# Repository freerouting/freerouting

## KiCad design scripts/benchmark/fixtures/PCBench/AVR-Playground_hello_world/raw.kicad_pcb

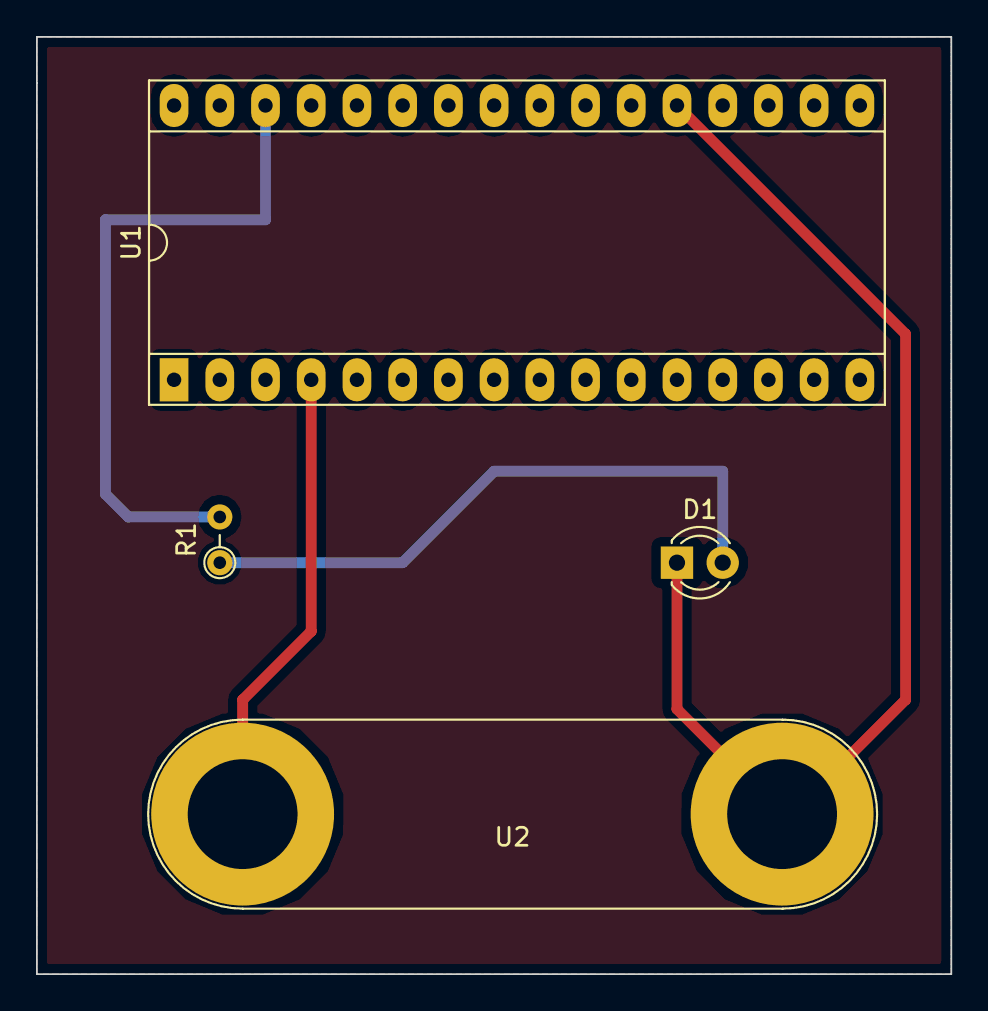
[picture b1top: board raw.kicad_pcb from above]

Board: 2 copper layers, 50.8 x 52.1 mm, 4 parts (0 on the bottom side), 4 nets.

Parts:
D1: LED; LED_D3.0mm
R1: 1k; R_Axial_DIN0204_L3.6mm_D1.6mm_P2.54mm_Vertical
U1: ATMEGA328P-AU; DIP-32_W15.24mm_Socket_LongPads
U2: myConn2; Banana_Jack_2Pin

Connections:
+5V: U1.4, U2.1
GND: D1.1, U1.21, U2.2
unnamed: D1.2, R1.1
unnamed: R1.2, U1.30

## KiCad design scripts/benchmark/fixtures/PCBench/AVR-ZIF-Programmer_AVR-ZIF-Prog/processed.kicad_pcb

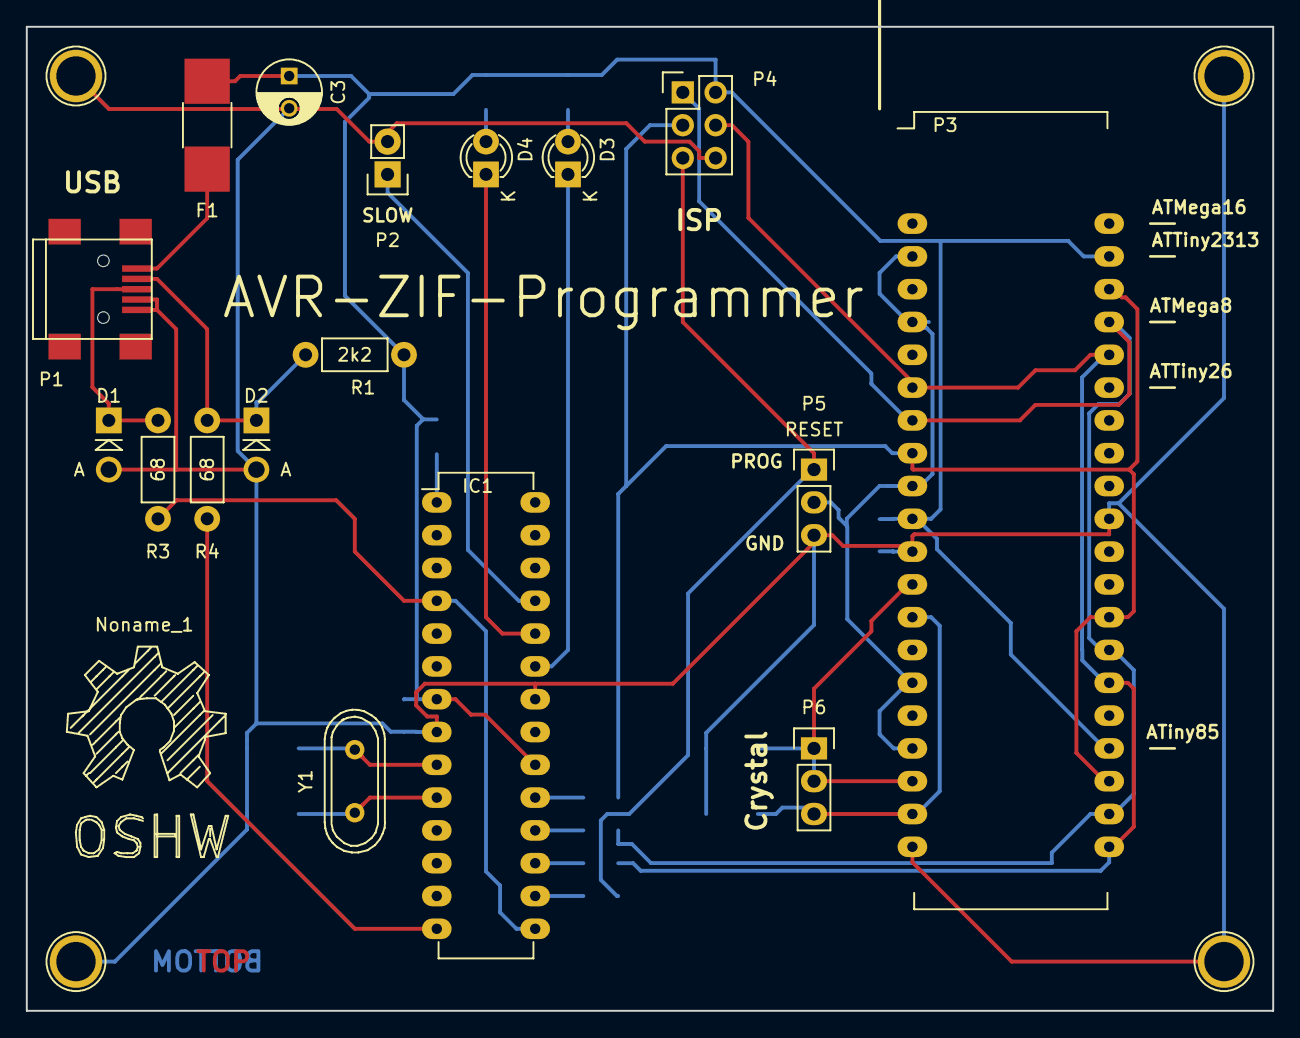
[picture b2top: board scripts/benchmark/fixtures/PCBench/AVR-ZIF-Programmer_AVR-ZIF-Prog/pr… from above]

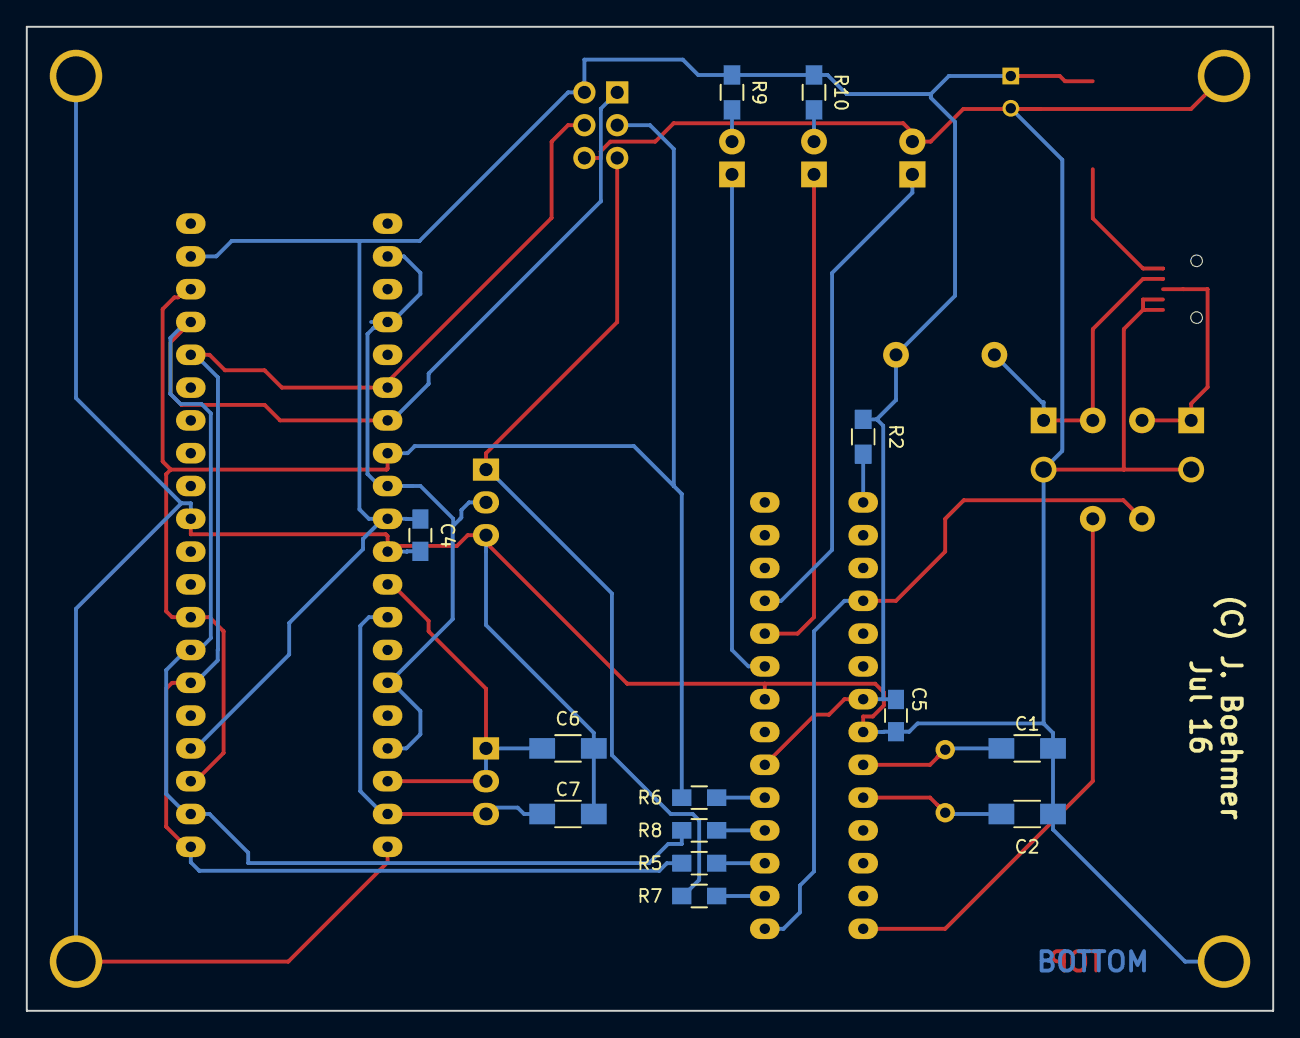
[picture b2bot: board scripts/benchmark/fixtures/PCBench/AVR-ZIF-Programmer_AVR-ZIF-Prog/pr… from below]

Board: 2 copper layers, 96.5 x 76.2 mm, 35 parts (13 on the bottom side), 26 nets.

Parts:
C1, C2, C6, C7: 15p; C_1206_HandSoldering
C3: 10u; C_Radial_D5_L6_P2.5
C4, C5: 100n; C_0805_HandSoldering
D1, D2: 3V6; Diode_DO-41_SOD81_Vertical_AnodeUp
D3: green; LED-3MM
D4: red; LED-3MM
F1: Poly 500mA; R_1812_HandSoldering
IC1: ATMEGA8-P; DIP-28_W7.62mm_LongPads
Noname_1: Symbol_OSHW-Logo_SilkScreen_BIG
P1: USB_B; USB_Mini-B
P2: SLOW_SCK; Pin_Header_Straight_1x02
P3: ZIF40; ZIF-40_W15.24mm_LongPads
P4: AVR-ISP; Pin_Header_Straight_2x03
P5: RESET; Pin_Header_Straight_1x03
P6: XTAL; Socket_Strip_Straight_1x03
P7, P8, P9, P10: MOUNT; 1pin
R1: 2k2; Resistor_Horizontal_RM7mm
R2: 10k; R_0805_HandSoldering
R3, R4: 68; Resistor_Horizontal_RM7mm
R5, R6, R7, R8: 220; R_0805_HandSoldering
R9, R10: 1k; R_0805_HandSoldering
Y1: 12MHz; Crystal_HC49-U_Vertical

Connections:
/D+: IC1.4, IC1.15, R3.1
/D-: IC1.14, R4.1
/LED1: D3.1, IC1.23
/LED2: D4.1, IC1.24
/MISO: P3.7, P3.22, P3.27, P3.37, P4.1, R8.2
/MOSI: P3.6, P3.21, P3.26, P3.36, P4.4, R5.2
/RST: P3.2, P3.4, P3.9, P3.15, P3.17, P5.2
/RST1: P4.5, P5.1, R7.2
/SCK: P3.8, P3.23, P3.28, P3.38, P4.3, R6.2
/SLOW: IC1.25, P2.1
/XTAL1: C6.1, P3.12, P3.18, P6.1, P6.2
/XTAL2: C7.1, P3.13, P3.19, P6.3
GND: C1.2, C2.1, C3.2, C4.2, C5.2, C6.2, C7.2, D1.2, D2.2, IC1.8, IC1.22, P1.4, P1.5, P2.2, P3.11, P3.20, P3.31, P4.6, P5.3, P7.1, P8.1, P9.1, P10.1
unnamed: C1.1, IC1.9, Y1.2
unnamed: C2.2, IC1.10, Y1.1
unnamed: D1.1, P1.3, R3.2
unnamed: D2.1, P1.2, R1.2, R4.2
unnamed: D3.2, R9.2
unnamed: D4.2, R10.2
unnamed: F1.2, P1.1
unnamed: IC1.1, R2.2
unnamed: IC1.16, R7.1
unnamed: IC1.17, R5.1
unnamed: IC1.18, R8.1
unnamed: IC1.19, R6.1
VCC: C3.1, C4.1, C5.1, F1.1, IC1.7, IC1.20, P3.10, P3.24, P3.39, P4.2, R1.1, R2.1, R9.1, R10.1

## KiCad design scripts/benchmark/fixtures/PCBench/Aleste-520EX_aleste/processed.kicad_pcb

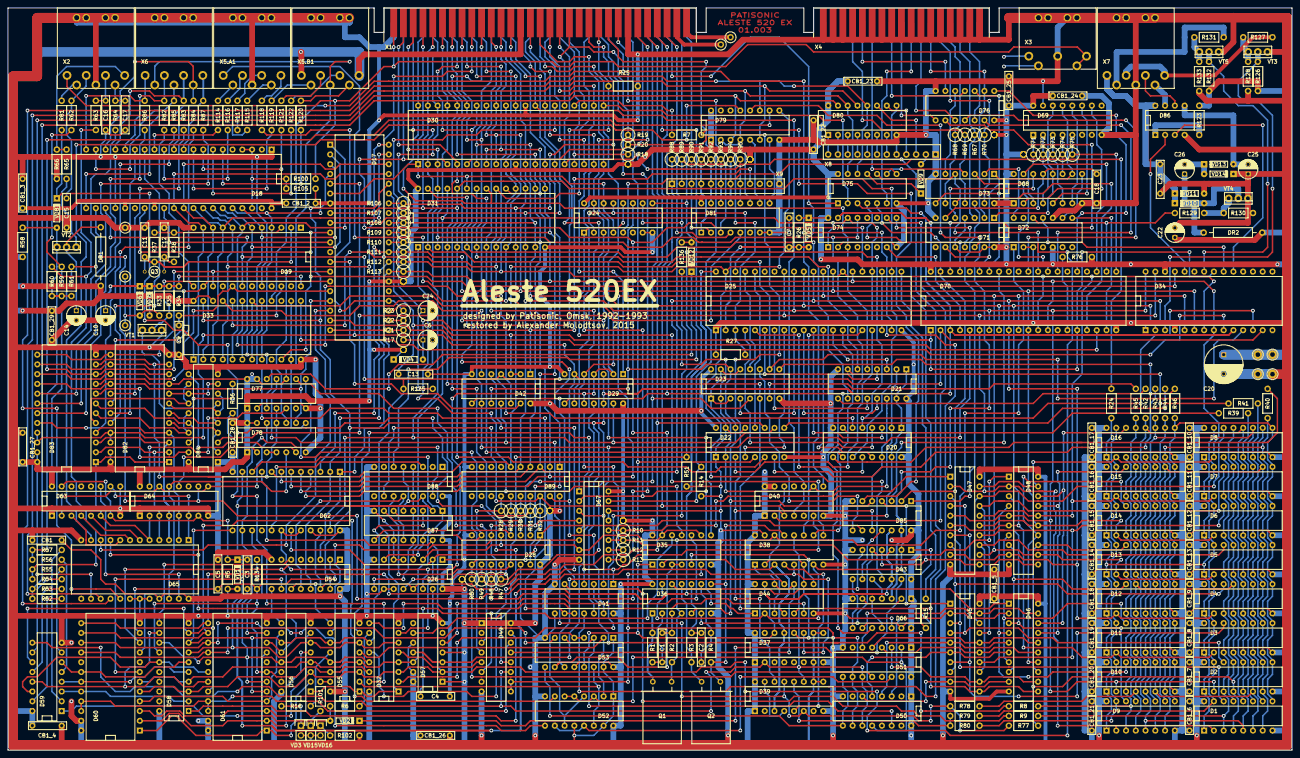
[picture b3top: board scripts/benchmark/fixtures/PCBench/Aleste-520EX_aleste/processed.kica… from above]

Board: 2 copper layers, 334.0 x 193.0 mm, 313 parts (0 on the bottom side), 451 nets.

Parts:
C1, C2, C3, C4, C5, C7, C9, C11, C12, C13, C15, C16, C17, C18, C23: CAP; C_Disc_D7.5_P2.5
C6, C10, C14, C22, C24, C25, C26: CAPP; C_Radial_D5_L6_P2.5
C20: CAPP; C_Radial_D10_L16_P5
CB1, CB1_2, CB1_3, CB1_4, CB1_5, CB1_6, CB1_7, CB1_8, CB1_9, CB1_10, CB1_11, CB1_12, CB1_13, CB1_14, CB1_15, CB1_16, CB1_17, CB1_18, CB1_19, CB1_20, CB1_21, CB1_22, CB1_23, CB1_24, CB1_25, CB1_26, CB1_27, CB1_28, CB1_29: CAP; C_Disc_D7.5_P2.5
D1, D2, D3, D4, D5, D6, D7, D8, D9, D10, D11, D12, D13, D14, D15, D16: 565РУ7; DIP-16
D17: 580ВВ55; DIP-40
D18: AY-3-8910; DIP-40
D19: 512ВИ1; DIP-24
D20, D21, D22, D23, D52, D53: 555КП2; DIP-16
D24, D81: 555КП7; DIP-16
D25: 1809ВГ6; DIP-40
D26: 555КП12; DIP-16
D28, D67: 556РТ4; DIP-16
D29, D44: 555ЛЛ1; DIP-14
D30: Z80; DIP-40
D31: 27512; DIP-28
D32, D55, D56, D59, D68, D79: 555ТМ9; DIP-16
D33: 580ВИ53; DIP-24
D34: 580ВВ51; DIP-28
D35, D85: 555ЛИ1; DIP-14
D36, D42, D73: 555ЛН1; DIP-14
D37: 555ИЕ10; DIP-16
D38: 555КП11; DIP-16
D39, D49, D50, D51: 555ИР11; DIP-16
D40, D57, D66, D71, D77: 555ТМ2; DIP-14
D41, D75, D78: 555ЛА3; DIP-14
D43: 555ЛЕ1; DIP-14
D45, D46, D47, D48: 555ИР22; DIP-20
D54, D74: 555ИД4; DIP-16
D58, D84: 555ИР23; DIP-20
D60, D61, D82, D83: 1802ИР1; DIP-24
D62, D65: 573РФ2; DIP-24
D63, D64: 561ИЕ10; DIP-16
D69: 155РЕ3; DIP-16
D70: 1810ВГ72; DIP-40
D72: 555ИЕ5; DIP-14
D76: 555ЛН2; DIP-14
D80: 555ИД10; DIP-16
D86: 170АП2; DIP-8
D87, D88: 555ИР32; DIP-16
D89: 555АП6; DIP-20
DR1, DR2: INDUCTOR; Choke_Horizontal_RM15mm
P1, P2, P3, P4, P5, P6, P7, P7_2, P8: PIN
Q1: 16 MHz; Crystal_HC49-U_Horizontal_Typ1
Q2: 13.333 MHz; Crystal_HC49-U_Horizontal_Typ1
Q3: QUARTZ; Crystal_Round_Vertical_5mm
R1, R2, R3, R4, R5, R6, R7, R8, R9, R14, R15, R16, R24, R25, R26, R27, R33, R34, R35, R36, R37, R38, R39, R40, R41, R42, R43, R44, R45, R46, R51, R52, R53, R54, R55, R56, R57, R58, R59, R60, R61, R62, R63, R64, R65, R66, R76, R77, R78, R79, R80, R81, R82, R83, R84, R85, R86, R87, R100, R101, R102, R105, R114, R115, R116, R117, R118, R119, R120, R121, R122, R123, R126, R127, R128, R129, R130, R131, R132, R133, R134, R135, R136: RES; Resistor_Horizontal_RM7.5mm
R10, R11, R12, R13, R17, R18, R19, R20, R21, R22, R23, R28, R29, R30, R31, R32, R47, R48, R49, R50, R67, R68, R69, R70, R71, R72, R73, R74, R75, R88, R89, R90, R91, R92, R93, R94, R95, R106, R107, R108, R109, R110, R111, R112, R113: RES; Resistor_Vertical_RM2.5mm
VD1, VD2, VD4, VD5, VD6, VD7, VD8, VD9, VD10, VD12, VD13, VD14: DIODE_MY; Diode_DO-35_SOD27_Horizontal_RM7.5
VD3, VD15, VD16: LED_MY; Pin_Header_Straight_1x02
VD11: ZDIODE_MY; Diode_DO-35_SOD27_Horizontal_RM7.5
VT1, VT2, VT3, VT4, VT5: NPN; KT315_KT361
X1: SLOT-62; SLOT_62
X2, X5.A1, X5.B1, X6, X7: CONN-7S; DNR-8F1R
X3: CONN-5S; DNR-5F1R
X4: SLOT-34
X8, X9: CONN-12; FB-12

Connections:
/AGND: P4.1, X1.A30
/AVCC: P3.1, X1.A31
/CPU/A0: D30.30, D31.10, D33.19, D41.2, D42.9, D67.3, D70.5, X1.B9
/CPU/A1: D20.6, D30.31, D31.9, D33.20, X1.A9
/CPU/A2: D20.10, D30.32, D31.8, X1.B8
/CPU/A3: D21.6, D30.33, D31.7, X1.A8
/CPU/A4: D21.10, D30.34, D31.6, X1.B7
/CPU/A5: D22.6, D30.35, D31.5, X1.A7
/CPU/A6: D23.6, D30.36, D31.4, D44.4, X1.B6
/CPU/A7: D21.11, D30.37, D31.3, D74.13, X1.A6
/CPU/A8: D17.9, D20.5, D25.24, D26.4, D30.38, D31.25, D34.12, D74.1, D74.14, X1.B5
/CPU/A9: D17.8, D20.11, D25.22, D26.12, D30.39, D31.24, X1.A5
/CPU/A10: D21.5, D30.40, D31.21, D74.3, X1.B4
/CPU/A11: D17.6, D24.4, D24.14, D30.1, D31.23, X1.A4
/CPU/A12: D23.10, D30.2, D31.2, D34.11, X1.B3
/CPU/A13: D22.10, D29.13, D30.3, D31.26, D62.23, X1.A3
/CPU/A14: D25.25, D26.3, D28.5, D30.4, D35.9, D35.13, D67.7, X1.B2
/CPU/A15: D26.13, D28.6, D30.5, D54.14, D62.22, D67.4, D89.1, X1.A2
/CPU/BUFFER0: D47.1, D67.12, R10.1
/CPU/BUFFER1: D48.1, D67.11, R11.1
/CPU/CLK: D30.6, D39.14, D40.3, R20.1, X1.B25
/CPU/D0: D1.2, D9.2, D17.34, D25.33, D30.14, D31.11, D34.27, D47.2, D48.2, D62.8, D70.6, D89.6, R106.1, X1.B13
/CPU/D1: D2.2, D10.2, D17.33, D25.32, D30.15, D31.12, D34.28, D47.5, D48.5, D62.7, D70.7, D89.5, R107.1, X1.A13
/CPU/D2: D3.2, D11.2, D17.32, D25.31, D30.12, D31.13, D34.1, D47.6, D48.6, D62.6, D70.8, D89.4, R108.1, X1.B12
/CPU/D3: D4.2, D12.2, D17.31, D25.30, D30.8, D31.15, D34.2, D47.9, D48.9, D62.5, D70.9, D89.3, R109.1, X1.A12
/CPU/D4: D5.2, D13.2, D17.30, D25.29, D30.7, D31.16, D34.5, D47.12, D48.12, D62.4, D70.10, D89.2, R110.1, X1.B11
/CPU/D5: D6.2, D14.2, D17.29, D25.28, D30.9, D31.17, D34.6, D47.15, D48.15, D62.3, D70.11, R111.1, X1.A11
/CPU/D6: D7.2, D15.2, D17.28, D25.27, D30.10, D31.18, D34.7, D47.16, D48.16, D54.13, D62.2, D70.12, R112.1, X1.B10
/CPU/D7: D8.2, D16.2, D17.27, D25.26, D30.13, D31.19, D34.8, D47.19, D48.19, D54.3, D62.1, D70.13, R113.1, X1.A10
/CPU/HY: C3.1, D25.40, D43.12, D85.12
/CPU/LOP: D43.10, D66.4
/CPU/PROM0: D55.7, D67.5
/CPU/PROM1: D55.10, D67.6
/CPU/RAMDIS: D67.15, R14.2, X1.A23
/CPU/ROM0: D35.10, D57.5
/CPU/ROM1: D35.12, D57.9
/CPU/ROMDIS: D31.22, R25.1, X1.A22
/CPU/SINT: D66.3, D79.12, D85.13
/CPU/~BUSAK: D30.23, X1.B19
/CPU/~BUSRQ: D30.25, R19.1, X1.A19
/CPU/~HALT: D30.18, X1.B17
/CPU/~INT: D30.16, R15.2, X1.A18
/CPU/~INTA: D29.8, D66.10, X1.A29
/CPU/~IORD: D17.5, D29.6, D34.13, D41.13, D70.2, D82.21, D82.22, D83.21, D83.22, D89.19
/CPU/~IORQ: D26.14, D29.2, D29.4, D29.10, D30.20, D62.18, D62.20, X1.A16
/CPU/~IOWR: D17.36, D29.3, D29.12, D33.23, D34.10, D41.12, D54.15, D70.3, D74.15
/CPU/~M1: D29.9, D30.27, X1.A15
/CPU/~MREQ: D30.19, D44.1, D67.2, X1.B14
/CPU/~NMI: D30.17, R18.1, X1.B18
/CPU/~RAMEN: D67.9, R13.1, X1.B22
/CPU/~RD: D29.5, D30.21, D67.1, D75.2, X1.B16
/CPU/~RESET: D18.23, D19.18, D32.1, D42.4, D55.1, D56.1, R135.1, X1.A21
/CPU/~RESET*: C24.1, D30.26, R135.2
/CPU/~RFSH: D30.28, D40.4, D40.10, X1.B15
/CPU/~ROMEN: D31.20, D67.10, R12.1, X1.B21
/CPU/~WAIT: D30.24, R7.2
/CPU/~WR: D29.1, D30.22, X1.A17
/Clocks & CRTC/1CY: D64.12, D78.2
/Clocks & CRTC/1M: D18.22, D37.11, D38.5, D64.10
/Clocks & CRTC/2CY: D64.13, D65.22, D78.5
/Clocks & CRTC/2M: D37.12, D38.2, D38.6, D44.9
/Clocks & CRTC/3CY: D63.2, D64.9, D64.14, D78.12
/Clocks & CRTC/4M: D35.2, D37.13, D38.3, D39.3
/Clocks & CRTC/8M: D35.1, D37.14, D44.13, D53.13
/Clocks & CRTC/13MHZ: D36.8, D38.13, Q2.1, R4.2
/Clocks & CRTC/16MHZ: D36.4, D38.14, D72.1, Q1.1, R2.2
/Clocks & CRTC/CAS: D39.12, R79.1, R80.1
/Clocks & CRTC/CBUF: D25.21, D43.4, D47.11, D48.11
/Clocks & CRTC/CURSOR: D25.19, D33.16, X1.B23
/Clocks & CRTC/DEN: D25.18, D77.12
/Clocks & CRTC/HIGHT: D38.1, D44.10, D44.12, D49.13
/Clocks & CRTC/HX: D25.39, D33.18, D43.11, D77.3, D79.9
/Clocks & CRTC/HY*: D17.18, D65.10
/Clocks & CRTC/KK0: D65.14, D79.3, D80.15
/Clocks & CRTC/KK1: D65.15, D75.13, D79.4, D80.14
/Clocks & CRTC/KK2: D65.16, D79.6, D80.13
/Clocks & CRTC/KK3: D65.17, D75.12, D79.11, D80.12
/Clocks & CRTC/L0: D24.2, D24.13, D25.38
/Clocks & CRTC/L1: D23.12, D25.37
/Clocks & CRTC/L2: D22.12, D25.36
/Clocks & CRTC/L.PEN: D25.3, R27.2, X1.A24
/Clocks & CRTC/MK0: D63.6, D64.2, D65.5, D82.1, D83.1
/Clocks & CRTC/MK1: D64.3, D65.4, D82.2, D83.2
/Clocks & CRTC/MK2: D64.4, D65.3, D82.3, D83.3
/Clocks & CRTC/MK3: D64.5, D65.2, D82.4, D83.4
/Clocks & CRTC/RAS: D39.6, D39.13, D42.11, D77.11, R77.1, R78.1
/Clocks & CRTC/SINT*: D65.11, D79.13
/Clocks & CRTC/SYNC*: C4.2, D49.6, D65.9
/Clocks & CRTC/V1: D20.4, D25.4
/Clocks & CRTC/V2: D20.12, D25.5
/Clocks & CRTC/V3: D21.4, D25.6
/Clocks & CRTC/V4: D21.12, D25.7
/Clocks & CRTC/V5: D22.4, D25.8
/Clocks & CRTC/V6: D23.4, D25.9
/Clocks & CRTC/V7: D21.13, D25.10
/Clocks & CRTC/V8: D20.3, D25.11
/Clocks & CRTC/V9: D20.13, D25.12
/Clocks & CRTC/V10: D21.3, D25.13
/Clocks & CRTC/V11: D25.14, D38.10
/Clocks & CRTC/V13: D25.16, D38.11
/Clocks & CRTC/V14: D22.3, D25.17
/Clocks & CRTC/V1113: D24.1, D24.12, D38.9
/Clocks & CRTC/VCLK: D36.13, D38.7, D43.2, D44.2, D45.1, D85.4
/Clocks & CRTC/XTAL: D37.2, D38.12, D39.11, D49.11, D50.11, D51.11, D59.9
/Clocks & CRTC/~3CY: D77.4, D78.11, D82.11, D83.11
/Clocks & CRTC/~RESET2: C7.2, D25.2, R26.1, VD5.2
/FDC/DISCINT: D17.19, D70.18
/FDC/DSKRDY: D70.35, D71.9, D76.3
/FDC/DW: D70.22, D72.12, R129.1
/FDC/EXRG: D44.5, D74.10
/FDC/FP0: D68.3, D69.1, R71.1
/FDC/FP1: D68.4, D69.2, R72.1
/FDC/FP2: D68.6, D69.3, R73.1
/FDC/FP3: D68.11, D69.4, R74.1
/FDC/RDD: D68.15, D70.23
/FDC/RESET: C13.2, D17.35, D34.21, D42.2, D42.3, D70.1, D70.16
/FDC/RSCLK: D34.20, D72.11
/FDC/RW/S: D70.39, D75.5, D85.2
/FDC/WGPTCLK: D70.19, D72.8
/FDC/WRC: D69.5, D70.21, R75.1
/FDC/XD0: D32.3, D55.3, D56.3, D57.2, D58.3, D60.5, D62.9, D71.12, D87.15
/FDC/~DIR: D76.8, X4.A9
/FDC/~DRIVE0: D76.6, X4.A5
/FDC/~DRIVE1: D75.8, X4.A6
/FDC/~GATE: D71.2, D76.2, X4.A12
/FDC/~INDEX: D73.11, R69.1, X4.A4
/FDC/~MOTOR: D76.4, X4.A8
/FDC/~RDATA: D71.3, R67.1, X4.A15
/FDC/~SIDE: D76.12, X4.A16
/FDC/~STEP: D75.6, X4.A10
/FDC/~TRAC0: D73.13, R70.1, X4.A13
/FDC/~WRDAT: D76.10, X4.A11
/FDC/~WRTPRT: D73.9, R68.1, X4.A14
/Gate Array/4ST: D35.3, D35.4, D53.10
/Gate Array/8ST: D44.11, D53.11
/Gate Array/"A": D26.7, D87.5, D87.14, D88.5, D88.14
/Gate Array/"B": D26.9, D87.4, D87.13, D88.4, D88.13
/Gate Array/B: C15.1, R62.1, X2.4
/Gate Array/BLAKS: D32.10, R6.2
/Gate Array/BLANK: D59.1, R6.1, VD2.2
/Gate Array/C0: D58.2, D59.3, D60.20
/Gate Array/C1: D58.5, D59.4, D60.19
/Gate Array/C2: D58.6, D59.6, D60.18
/Gate Array/C3: D58.9, D59.11, D61.20
/Gate Array/C4: D58.12, D59.13, D61.19
/Gate Array/C5: D58.15, D59.14, D61.18
/Gate Array/CBORDER: D54.6, D58.11
/Gate Array/COLOR: C5.2, D54.2, D60.11, D61.11, R134.1
/Gate Array/CS53: D32.12, D42.5
/Gate Array/G: C16.1, R63.1, X2.5
/Gate Array/HIGHTX: D32.5, D49.5
/Gate Array/HIGHTY: D32.2, R136.2
/Gate Array/HIGHTZ: D24.9, R136.1, VD12.2, X1.B31
/Gate Array/LED0: D55.12, R16.1
/Gate Array/LED1: D55.15, R101.1
/Gate Array/LUM: R65.2, R66.2, X2.7
/Gate Array/M0: D28.7, D87.10, D89.14, R28.1
/Gate Array/M1: D28.4, D87.9, D89.15, R29.1
/Gate Array/M2: D28.3, D87.7, D89.16, R30.1
/Gate Array/M3: D28.2, D87.6, D89.17, R31.1
/Gate Array/M4: D28.15, D85.10, D88.10, D89.18, R32.1, X1.A28
/Gate Array/MAP14: D24.3, D24.15, D28.12, R47.1, X1.A26
/Gate Array/MAP15: D22.5, D28.11, R48.1, X1.B26
/Gate Array/MAP16: D22.11, D28.10, R49.1, X1.A27
/Gate Array/MAP17: D23.5, D28.9, R50.1, X1.B27
/Gate Array/MAP18: D23.11, D85.8
/Gate Array/MAPBLK: D28.13, D88.11, R51.2, X1.B28
/Gate Array/MAPER: D54.12, D87.12, D88.12
/Gate Array/MAPMOD: D26.2, D28.1, D32.7, D62.19, D85.9
/Gate Array/MODE: D54.11, D55.9
/Gate Array/MODE0: D52.14, D53.14, D55.2
/Gate Array/MODE1: D52.2, D53.2, D55.5
/Gate Array/MVI: D35.6, D49.9, D49.10, D50.10, D51.10
/Gate Array/NCOLOR: D54.9, D56.9
/Gate Array/NCOLOR0: D56.2, D60.1, D61.1
/Gate Array/NCOLOR1: D56.5, D60.2, D61.2
/Gate Array/NCOLOR2: D56.7, D60.3, D61.3
/Gate Array/NCOLOR3: D56.10, D60.4, D61.4
/Gate Array/NCOLOR4: D54.1, D56.12, D60.10, D61.10
/Gate Array/PAGE: D49.15, D58.1
/Gate Array/PX0: D51.12, D60.13, D61.13
/Gate Array/PX1: D52.7, D60.14, D61.14
/Gate Array/PX2: D52.9, D60.15, D61.15
/Gate Array/PX3: D53.7, D60.16, D61.16
/Gate Array/R: C17.1, R64.1, X2.3
/Gate Array/RRC: D50.9, D51.9, D53.9
/Gate Array/SOUND: R100.2, X1.A1, X2.6, X3.3, X3.5
/Gate Array/SYNC: D49.12, R81.1, VD8.1
/Gate Array/VD0: D45.2, D46.2, D50.3
/Gate Array/VD1: D45.5, D46.5, D50.4
/Gate Array/VD2: D45.6, D46.6, D50.5
/Gate Array/VD3: D45.9, D46.9, D50.6
/Gate Array/VD4: D45.12, D46.12, D51.3
/Gate Array/VD5: D45.15, D46.15, D51.4
/Gate Array/VD6: D45.16, D46.16, D51.5
/Gate Array/VD7: D45.19, D46.19, D51.6
/Gate Array/VRAMACC: D62.17, D88.3
/Gate Array/XD1: D32.4, D55.4, D56.4, D57.12, D58.4, D60.6, D62.10, D87.1
/Gate Array/XD2: D32.6, D55.6, D56.6, D58.7, D60.7, D62.11, D87.2
/Gate Array/XD3: D32.11, D55.11, D56.11, D58.8, D61.5, D62.13, D87.3
/Gate Array/XD4: D32.13, D55.13, D56.13, D58.13, D61.6, D62.14, D88.15
/Gate Array/XD5: D32.14, D55.14, D58.14, D61.7, D62.15
/Gate Array/~CSAY: D32.15, R36.1
/Gate Array/~FUTURE: D41.8, D52.4, D52.11
/Gate Array/~PAGE: D49.14, D60.21, D60.22, D61.21, D61.22
/Periphery/50/60: D17.22, R22.1
/Periphery/+12V: C23.2, D86.8, VD10.1, VD11.1, X7.6
/Periphery/-12V: C25.2, D86.5, VD13.2
/Periphery/AY0: D17.4, D18.37, D19.4, D33.8
/Periphery/AY1: D17.3, D18.36, D19.5, D33.7
/Periphery/AY2: D17.2, D18.35, D19.6, D33.6
/Periphery/AY3: D17.1, D18.34, D19.7, D33.5
/Periphery/AY4: D17.40, D18.33, D19.8, D33.4
/Periphery/AY5: D17.39, D18.32, D19.9, D33.3
/Periphery/AY6: D17.38, D18.31, D19.10, D33.2
/Periphery/AY7: D17.37, D18.30, D19.11, D33.1
/Periphery/BC1: D17.11, D18.29
/Periphery/BDIR: D17.10, D18.27
/Periphery/BUSY: D17.24, R23.1, R118.1
/Periphery/COMMON: D78.8, X5.B1.2, X6.1
/Periphery/DSR: D34.22, R132.2, VT5.C
/Periphery/DSR*: R131.1, X7.1
/Periphery/DTR: D34.24, D86.2
/Periphery/DTR*: D86.7, X7.3
/Periphery/FUTURE: D33.17, D41.9, D41.10
/Periphery/KM0: D80.1, X8.12
/Periphery/KM1: D80.2, X8.11
/Periphery/KM2: D80.3, X8.10
/Periphery/KM3: D80.4, X8.9
/Periphery/KM4: D80.5, X8.8
/Periphery/KM5: D80.6, X8.7
/Periphery/KM6: D80.7, X8.6
/Periphery/KM7: D80.9, X8.5
/Periphery/KM8: D80.10, X8.4
/Periphery/KM9: D80.11, X8.3
/Periphery/KM10: VD9.2, X8.2
/Periphery/KM11: D81.4, R88.1, X9.1
/Periphery/KM12: D81.3, R89.1, X9.2
/Periphery/KM13: D81.2, R90.1, X9.3
/Periphery/KM14: D81.1, R91.1, X9.4
/Periphery/KM15: D81.15, R92.1, X9.5
/Periphery/KM16: D81.14, R93.1, X9.6
/Periphery/KM17: D81.13, R94.1, X9.7
/Periphery/KM18: D81.12, R95.1, X9.8
/Periphery/KRS: D81.5, D84.3
/Periphery/KW0: D79.2, D81.11
/Periphery/KW1: D79.5, D81.10
/Periphery/KW2: D79.7, D81.9
/Periphery/KW3: D79.10, D82.10, D83.10
/Periphery/PB2: D17.20, D17.21, R21.1
/Periphery/PD0: D18.13, R114.1
/Periphery/PD1: D18.12, R116.1
/Periphery/PD2: D18.11, R117.1
/Periphery/PD3: D18.10, R115.1
/Periphery/PD4: D18.9, R119.1
/Periphery/PD5: D18.8, R121.1
/Periphery/PD6: D18.7, R122.1
/Periphery/PD7: D18.6, R120.1
/Periphery/RXC: D33.10, D34.25
/Periphery/RXD: D34.3, R126.1, VT3.C
/Periphery/SABC: D18.3, D18.4, D18.38, R100.1, R105.2
/Periphery/SBRES: C6.1, D42.1, R17.1, VD4.2, X9.9
/Periphery/STROBE: D17.13, D42.13
/Periphery/TXC: D33.13, D34.9
/Periphery/TXD: D34.19, D86.3
/Periphery/TXD*: D86.6, X7.5
/Periphery/VC1: C10.1, D19.24, R33.1, R34.2, R35.2, VD6.1, VD7.1
/Periphery/X1: D18.21, R87.2, X6.7
/Periphery/X2: D18.20, R86.2, X6.6
/Periphery/X3: D18.19, R85.2, X6.2
/Periphery/X4: D18.18, R84.2, X6.3
/Periphery/X5: D18.17, R83.2, X6.5
/Periphery/X6: D18.16, R82.2, X6.4
/Periphery/X7: D18.15, D82.19
/Periphery/X8: D18.14, D82.20
/Periphery/Y0: D17.14, D19.15, D78.10, D82.13, D83.13
/Periphery/Y1: D17.15, D19.14, D82.14, D83.14
/Periphery/Y2: D17.16, D19.17, D82.15, D83.15
/Periphery/Y3: D17.17, D78.9, D82.16, D83.16
/Periphery/Z0: D82.5, D84.2, D84.4
/Periphery/Z1: D82.6, D84.5, D84.7
/Periphery/Z2: D82.7, D84.6, D84.8
/Periphery/Z3: D82.8, D84.9, D84.13
/Periphery/Z4: D83.5, D84.12, D84.14
/Periphery/Z5: D83.6, D84.15, D84.17
/Periphery/Z6: D83.7, D84.16, D84.18
/Periphery/Z7: D83.8, D84.19
/Periphery/~CS53: D33.21, D42.6
/Periphery/~STROBE: D42.12, X5.A1.6
/RAM/CAS0: D1.15, D2.15, D3.15, D4.15, D5.15, D6.15, D7.15, D8.15, R79.2
/RAM/CAS1: D9.15, D10.15, D11.15, D12.15, D13.15, D14.15, D15.15, D16.15, R80.2
/RAM/DIS: D20.2, D21.2, D22.2, D23.2, D24.10, D40.9, X1.B30
/RAM/MA0: D1.5, D2.5, D3.5, D4.5, D5.5, D6.5, D7.5, D8.5, D9.5, D10.5, D11.5, D12.5, D13.5, D14.5, D15.5, D16.5, R39.2
/RAM/MA1: D1.7, D2.7, D3.7, D4.7, D5.7, D6.7, D7.7, D8.7, D9.7, D10.7, D11.7, D12.7, D13.7, D14.7, D15.7, D16.7, R40.2
/RAM/MA2: D1.6, D2.6, D3.6, D4.6, D5.6, D6.6, D7.6, D8.6, D9.6, D10.6, D11.6, D12.6, D13.6, D14.6, D15.6, D16.6, R41.2
/RAM/MA3: D1.12, D2.12, D3.12, D4.12, D5.12, D6.12, D7.12, D8.12, D9.12, D10.12, D11.12, D12.12, D13.12, D14.12, D15.12, D16.12, R42.2
/RAM/MA4: D1.11, D2.11, D3.11, D4.11, D5.11, D6.11, D7.11, D8.11, D9.11, D10.11, D11.11, D12.11, D13.11, D14.11, D15.11, D16.11, R43.2
/RAM/MA5: D1.10, D2.10, D3.10, D4.10, D5.10, D6.10, D7.10, D8.10, D9.10, D10.10, D11.10, D12.10, D13.10, D14.10, D15.10, D16.10, R44.2
/RAM/MA6: D1.13, D2.13, D3.13, D4.13, D5.13, D6.13, D7.13, D8.13, D9.13, D10.13, D11.13, D12.13, D13.13, D14.13, D15.13, D16.13, R45.2
/RAM/MA7: D1.9, D2.9, D3.9, D4.9, D5.9, D6.9, D7.9, D8.9, D9.9, D10.9, D11.9, D12.9, D13.9, D14.9, D15.9, D16.9, R46.2
/RAM/MA8: D1.1, D2.1, D3.1, D4.1, D5.1, D6.1, D7.1, D8.1, D9.1, D10.1, D11.1, D12.1, D13.1, D14.1, D15.1, D16.1, R24.2
/RAM/R0: D1.14, D45.3, D47.3
/RAM/R1: D2.14, D45.4, D47.4
/RAM/R2: D3.14, D45.7, D47.7
/RAM/R3: D4.14, D45.8, D47.8
/RAM/R4: D5.14, D45.13, D47.13
/RAM/R5: D6.14, D45.14, D47.14
/RAM/R6: D7.14, D45.17, D47.17
/RAM/R7: D8.14, D45.18, D47.18
/RAM/R8: D9.14, D46.3, D48.3
/RAM/R9: D10.14, D46.4, D48.4
/RAM/R10: D11.14, D46.7, D48.7
/RAM/R11: D12.14, D46.8, D48.8
/RAM/R12: D13.14, D46.13, D48.13
/RAM/R13: D14.14, D46.14, D48.14
/RAM/R14: D15.14, D46.17, D48.17
/RAM/R15: D16.14, D46.18, D48.18
/RAM/RAS0: D1.4, D2.4, D3.4, D4.4, D5.4, D6.4, D7.4, D8.4, R77.2
/RAM/RAS1: D9.4, D10.4, D11.4, D12.4, D13.4, D14.4, D15.4, D16.4, R78.2
/RAM/S0: D20.14, D21.14, D22.14, D23.14, D24.11, D36.5, D42.10, D85.5
/RAM/VBUF: D43.1, D45.11, D46.11
/RAM/WE0: D1.3, D2.3, D3.3, D4.3, D5.3, D6.3, D7.3, D8.3, R9.2
/RAM/WE1: D9.3, D10.3, D11.3, D12.3, D13.3, D14.3, D15.3, D16.3, R8.2
/RAM/~DIS: D40.8, D75.1, X1.B29
/RAM/~VCLK: D36.12, D43.6, D46.1
GND: C4.1, C5.1, C6.2, C7.1, C9.1, C10.2, C11.1, C12.1, C13.1, C14.2, C15.2, C16.2, C17.2, C18.1, C20.2, C22.2, C23.1, C24.2, C25.1, CB1.1, CB1_2.1, CB1_3.1, CB1_4.1, CB1_5.1, CB1_6.1, CB1_7.1, CB1_8.1, CB1_9.1, CB1_10.1, CB1_11.1, CB1_12.1, CB1_13.1, CB1_14.1, CB1_15.1, CB1_16.1, CB1_17.1, CB1_18.1, CB1_19.1, CB1_20.1, CB1_21.1, CB1_22.1, CB1_23.1, CB1_24.1, CB1_25.1, CB1_26.1, CB1_27.1, CB1_28.1, CB1_29.1, D1.16, D2.16, D3.16, D4.16, D5.16, D6.16, D7.16, D8.16, D9.16, D10.16, D11.16, D12.16, D13.16, D14.16, D15.16, D16.16, D17.7, D17.23, D18.1, D18.24, D19.12, D19.20, D20.1, D20.8, D20.15, D21.1, D21.8, D21.15, D22.1, D22.8, D22.13, D22.15, D23.1, D23.3, D23.8, D23.13, D23.15, D24.7, D24.8, D25.1, D26.1, D26.5, D26.6, D26.8, D26.10, D26.11, D26.15, D28.8, D28.14, D29.7, D30.29, D31.14, D32.8, D33.12, D34.4, D35.7, D36.7, D37.8, D38.8, D38.15, D39.8, D40.7, D41.7, D42.7, D43.7, D44.7, D45.10, D46.10, D47.10, D48.10, D49.8, D50.8, D51.8, D52.1, D52.8, D52.12, D52.15, D53.1, D53.4, D53.5, D53.8, D53.15, D54.8, D55.8, D56.8, D57.7, D58.10, D59.8, D60.12, D61.12, D62.12, D63.1, D63.8, D63.9, D64.1, D64.8, D65.12, D65.18, D65.19, D65.20, D66.7, D66.12, D67.8, D67.13, D67.14, D68.8, D69.8, D69.15, D70.20, D71.7, D72.2, D72.3, D72.10, D73.7, D74.2, D74.8, D75.7, D76.7, D77.2, D77.7, D78.7, D79.8, D80.8, D81.7, D81.8, D82.12, D83.12, D84.1, D84.10, D85.7, D86.4, D87.8, D87.11, D88.8, D89.10, P2.1, P6.1, P8.1, R5.1, R14.1, R25.2, R27.1, R51.1, R66.1, R102.1, R105.1, R128.1, R130.1, R133.1, VD1.2, VD11.2, VD14.1, VT1.E, VT3.E, VT4.E, VT5.E, X1.A25, X1.B1, X2.2, X2.S, X3.2, X3.S, X4.B1, X4.B2, X4.B3, X4.B4, X4.B5, X4.B6, X4.B7, X4.B8, X4.B9, X4.B10, X4.B11, X4.B12, X4.B13, X4.B14, X4.B15, X4.B16, X4.B17, X5.A1.2, X5.A1.S, X5.B1.S, X6.S, X7.2, X7.S, X8.1, X9.12
unnamed: C1.1, D36.2, R1.2
unnamed: C1.2, D36.3, R2.1
unnamed: C2.1, D36.10, R3.2
unnamed: C2.2, D36.9, R4.1
unnamed: C3.2, D63.7, D63.15, D64.7, R5.2, VD1.1
unnamed: C9.2, D19.22, R34.1
unnamed: C11.2, D19.2, Q3.2, R37.1
unnamed: C12.2, Q3.1, R38.1
unnamed: C14.1, DR1.2, VT2.C
unnamed: C18.2, D68.13, D71.6
unnamed: C26.1, DR2.2, VD10.2, VT4.C
unnamed: C26.2, VD13.1, VD14.2
unnamed: D19.3, R37.2, R38.2
unnamed: D19.13, R35.1, VT1.C
unnamed: D20.7, R39.1
unnamed: D20.9, R40.1
unnamed: D21.7, R41.1
unnamed: D21.9, R42.1
unnamed: D22.7, R43.1
unnamed: D22.9, R44.1
unnamed: D23.7, R45.1
unnamed: D23.9, R46.1
unnamed: D24.5, R24.1
unnamed: D25.23, D41.11
unnamed: D29.11, D57.3, D57.11
unnamed: D31.1, D35.11
unnamed: D31.27, D35.8
unnamed: D32.9, D44.6
unnamed: D35.5, D44.8
unnamed: D36.1, Q1.2, R1.1
unnamed: D36.6, D43.3, D43.5
unnamed: D36.11, Q2.2, R3.1
unnamed: D38.4, D39.5
unnamed: D39.4, D39.15
unnamed: D40.2, D75.3
unnamed: D40.6, D41.1, D41.4
unnamed: D40.12, D44.3
unnamed: D41.3, R8.1
unnamed: D41.5, D42.8
unnamed: D41.6, R9.1
unnamed: D43.8, D66.8
unnamed: D43.9, D85.11
unnamed: D43.13, VD2.1
unnamed: D49.3, D77.9
unnamed: D49.4, D77.8
unnamed: D50.12, D51.2, D52.3, D52.5, D52.6
unnamed: D50.14, D53.3, D53.6
unnamed: D51.14, D52.10, D52.13
unnamed: D54.10, R134.2
unnamed: D59.2, R57.2
unnamed: D59.5, R56.2
unnamed: D59.7, R55.2
unnamed: D59.10, R54.2
unnamed: D59.12, R53.2
unnamed: D59.15, R52.2
unnamed: D63.3, D65.8
unnamed: D63.4, D65.7
unnamed: D63.5, D65.6
unnamed: D63.10, D64.6, D65.1
unnamed: D63.11, D65.23
unnamed: D64.15, D77.5
unnamed: D66.2, D66.6
unnamed: D66.5, D66.11
unnamed: D66.9, D66.13, R15.1
unnamed: D68.2, D69.10
unnamed: D68.5, D69.11
unnamed: D68.7, D69.12
unnamed: D68.9, D72.9
unnamed: D68.10, D69.13, D73.1
unnamed: D68.12, D69.14, D71.1
unnamed: D68.14, D71.5
unnamed: D70.4, D74.7
unnamed: D70.15, R76.2
unnamed: D70.17, D73.10
unnamed: D70.25, D76.1
unnamed: D70.27, D76.13
unnamed: D70.28, D73.3
unnamed: D70.29, D73.5, D75.10
unnamed: D70.30, D76.11
unnamed: D70.33, D85.3
unnamed: D70.34, D73.8
unnamed: D70.37, D75.4
unnamed: D70.38, D76.9
unnamed: D71.11, D74.9
unnamed: D72.14, D73.2
unnamed: D73.4, D75.9
unnamed: D73.6, D76.5
unnamed: D73.12, D85.1
unnamed: D75.11, VD9.1
unnamed: D78.3, D78.4
unnamed: D78.6, D84.11
unnamed: D82.17, R83.1
unnamed: D82.18, R82.1
unnamed: D83.17, R87.1
unnamed: D83.18, R86.1
unnamed: D83.19, R85.1
unnamed: D83.20, R84.1
unnamed: D85.6, R7.1
unnamed: D86.1, R123.1
unnamed: D88.6, VD12.1
unnamed: P7.1, P7_2.1, R33.2, VD6.2
unnamed: R16.2, VD3.1
unnamed: R36.2, VT1.B
unnamed: R52.1, R53.1, R59.2, R62.2
unnamed: R54.1, R55.1, R60.2, R63.2
unnamed: R56.1, R57.1, R61.2, R64.2
unnamed: R58.1, R59.1, R60.1, R61.1, VD8.2, VT2.B
unnamed: R65.1, VT2.E
unnamed: R81.2, X2.1
unnamed: R101.2, VD15.1
unnamed: R102.2, VD16.1
unnamed: R114.2, X5.A1.1
unnamed: R115.2, X5.A1.3
unnamed: R116.2, X5.A1.4
unnamed: R117.2, X5.A1.5
unnamed: R118.2, X5.A1.7
unnamed: R119.2, X5.B1.1
unnamed: R120.2, X5.B1.3
unnamed: R121.2, X5.B1.4
unnamed: R122.2, X5.B1.5
unnamed: R127.1, R128.2, VT3.B
unnamed: R127.2, X7.4, X7.7
unnamed: R129.2, R130.2, VT4.B
unnamed: R131.2, R133.2, VT5.B
VCC: C20.1, C22.1, CB1.2, CB1_2.2, CB1_3.2, CB1_4.2, CB1_5.2, CB1_6.2, CB1_7.2, CB1_8.2, CB1_9.2, CB1_10.2, CB1_11.2, CB1_12.2, CB1_13.2, CB1_14.2, CB1_15.2, CB1_16.2, CB1_17.2, CB1_18.2, CB1_19.2, CB1_20.2, CB1_21.2, CB1_22.2, CB1_23.2, CB1_24.2, CB1_25.2, CB1_26.2, CB1_27.2, CB1_28.2, CB1_29.2, D1.8, D2.8, D3.8, D4.8, D5.8, D6.8, D7.8, D8.8, D9.8, D10.8, D11.8, D12.8, D13.8, D14.8, D15.8, D16.8, D17.26, D18.25, D18.28, D18.40, D20.16, D21.16, D22.16, D23.16, D24.16, D25.20, D26.16, D28.16, D29.14, D30.11, D31.28, D32.16, D33.11, D33.14, D33.22, D33.24, D34.26, D35.14, D36.14, D37.1, D37.7, D37.9, D37.10, D37.16, D38.16, D39.1, D39.9, D39.10, D39.16, D40.1, D40.13, D40.14, D41.14, D42.14, D43.14, D44.14, D45.20, D46.20, D47.20, D48.20, D49.1, D49.16, D50.1, D50.16, D51.1, D51.16, D52.16, D53.12, D53.16, D54.16, D55.16, D56.16, D57.1, D57.4, D57.10, D57.13, D57.14, D58.20, D59.16, D60.9, D60.23, D60.24, D61.9, D61.23, D61.24, D62.21, D62.24, D63.16, D64.16, D65.21, D65.24, D66.1, D66.14, D67.16, D68.1, D68.16, D69.16, D70.40, D71.4, D71.10, D71.13, D71.14, D72.5, D73.14, D74.16, D75.14, D76.14, D77.1, D77.10, D77.13, D77.14, D78.1, D78.13, D78.14, D79.1, D79.16, D80.16, D81.16, D82.9, D82.23, D82.24, D83.9, D83.23, D83.24, D84.20, D85.14, D87.16, D88.16, D89.20, DR1.1, DR2.1, P1.1, P5.1, R10.2, R11.2, R12.2, R13.2, R17.2, R18.2, R19.2, R20.2, R21.2, R22.2, R23.2, R26.2, R28.2, R29.2, R30.2, R31.2, R32.2, R47.2, R48.2, R49.2, R50.2, R58.2, R67.2, R68.2, R69.2, R70.2, R71.2, R72.2, R73.2, R74.2, R75.2, R76.1, R88.2, R89.2, R90.2, R91.2, R92.2, R93.2, R94.2, R95.2, R106.2, R107.2, R108.2, R109.2, R110.2, R111.2, R112.2, R113.2, R123.2, R126.2, R132.1, VD3.2, VD4.1, VD5.1, VD7.2, VD15.2, VD16.2, X1.A14, X5.B1.6, X5.B1.7
